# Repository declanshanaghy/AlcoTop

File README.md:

= AUTHOR::
Declan Shanaghy <declan@shanaghy.com>

= DESCRIPTION:
AlcoTop is the XMas drinking cap everyone should have.
With an alcohol sensor and lots of LED's you will know when
you haven't had enough to drink and your way home will be lit before you.

= REQUIREMENTS:
Arduino IDE for loading software onto the chip.
Eagle CAD 6.0+ for reading circuit schematic

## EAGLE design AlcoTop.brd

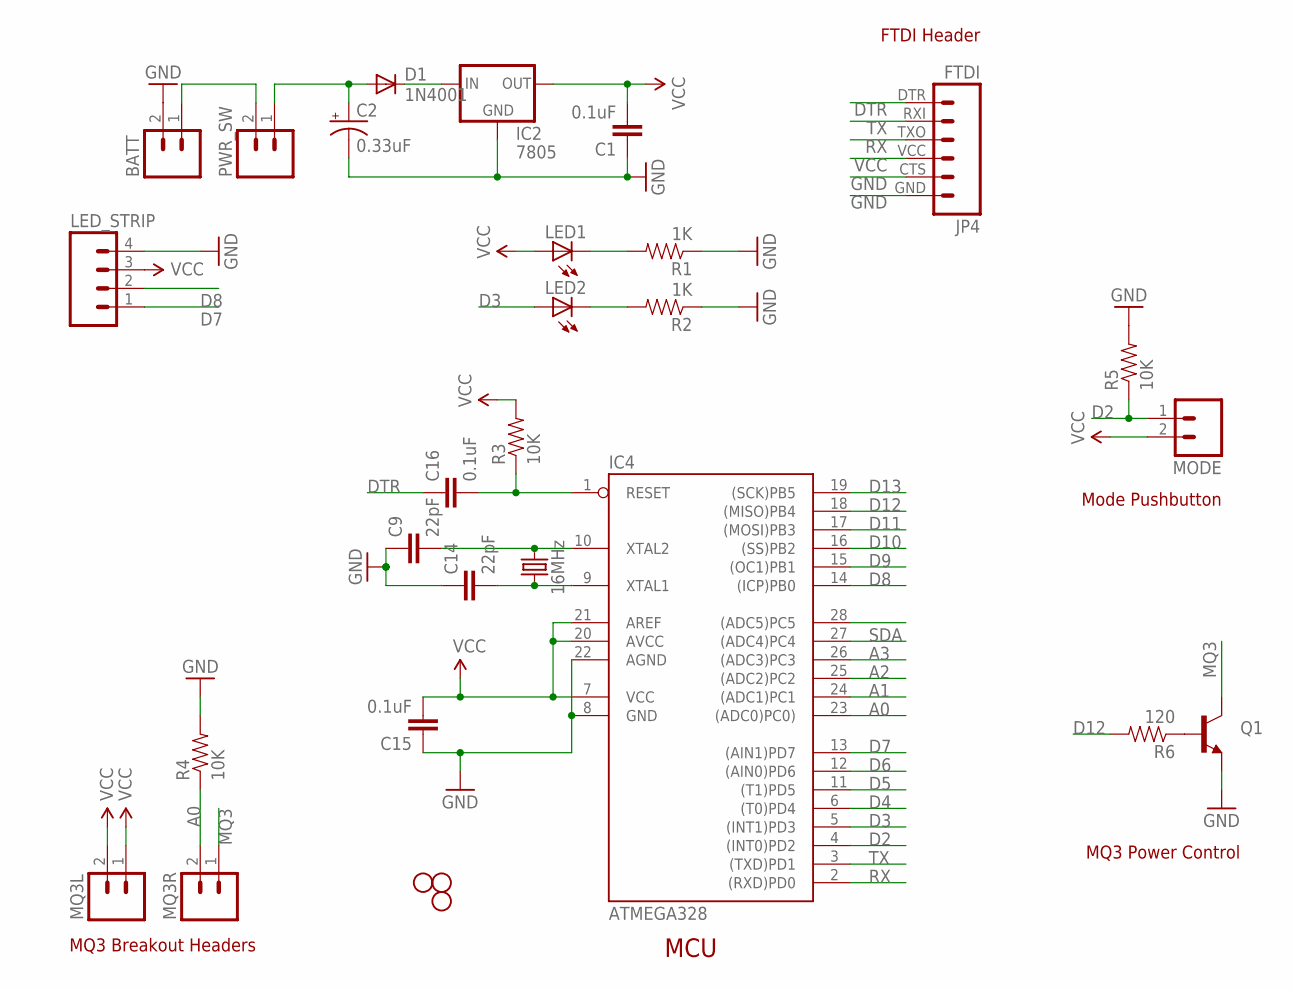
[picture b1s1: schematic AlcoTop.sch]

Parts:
BATT: M02LOCK_LONGPADS; 1X02_LOCK_LONGPADS
C1, C15, C16: 0.1uF; CAP-PTH-SMALL2
C2: 0.33uF; CPOL-RADIAL-10UF-25V
C9, C14: 22pF; CAP-PTH-SMALL2
D1: 1N4001; DIODE-1N4001
IC2: 7805; TO220-IGO
IC4: ATMEGA328; DIL28-3
JP1, JP2, JP6: STAND-OFF#2; STAND-OFF-#2
JP4: FTDI; FTDI_BASIC
LED1, LED2: LED5MM
LED_STRIP: M04LOCK_LONGPADS; 1X04_LOCK_LONGPADS
MODE: M02LOCK_LONGPADS; 1X02_LOCK_LONGPADS
MQ3L, MQ3R: M02LOCK_LONGPADS; 1X02_LOCK_LONGPADS
PWR_SW: M02LOCK_LONGPADS; 1X02_LOCK_LONGPADS
Q1: TRANSISTOR_NPNTO-92-AMMO; TO-92-AMMO
R1, R2: 1K; AXIAL-0.3
R3, R4, R5: 10K; AXIAL-0.3
R6: 120; AXIAL-0.3
Y1: 16MHz; HC49US

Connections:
A0: IC4.23 ((ADC0)PC0)), MQ3R.2, R4.P$1 (1)
A1: IC4.24 ((ADC1)PC1)
A2: IC4.25 ((ADC2)PC2)
A3: IC4.26 ((ADC3)PC3)
D2: IC4.4 ((INT0)PD2), MODE.1, R5.P$1 (1)
D3: IC4.5 ((INT1)PD3), LED2.A
D4: IC4.6 ((T0)PD4)
D5: IC4.11 ((T1)PD5)
D6: IC4.12 ((AIN0)PD6)
D7: IC4.13 ((AIN1)PD7), LED_STRIP.1
D8: IC4.14 ((ICP)PB0), LED_STRIP.2
D9: IC4.15 ((OC1)PB1)
D10: IC4.16 ((SS)PB2)
D11: IC4.17 ((MOSI)PB3)
D12: IC4.18 ((MISO)PB4), R6.P$2 (2)
D13: IC4.19 ((SCK)PB5)
DTR: C16.1, JP4.DTR (1)
GND: BATT.2, C1.1, C2.2 (-), C9.1, C14.1, C15.1, IC2.GND, IC4.8 (GND), IC4.22 (AGND), JP4.CTS (5), JP4.GND (6), LED_STRIP.4, Q1.1 (E), R1.P$1 (1), R2.P$1 (1), R4.P$2 (2), R5.P$2 (2)
MQ3: MQ3R.1, Q1.3 (C)
unnamed: LED1.K (C), R1.P$2 (2)
unnamed: BATT.1, PWR_SW.2
unnamed: C2.1 (+), D1.A, PWR_SW.1
unnamed: LED2.K (C), R2.P$2 (2)
unnamed: D1.C, IC2.IN
unnamed: Q1.2 (B), R6.P$1 (1)
RST: C16.2, IC4.1 (RESET), R3.P$1 (1)
RX: IC4.2 ((RXD)PD0), JP4.TXO (3)
SDA: IC4.27 ((ADC4)PC4)
TX: IC4.3 ((TXD)PD1), JP4.RXI (2)
VCC: C1.2, C15.2, IC2.OUT, IC4.7 (VCC), IC4.20 (AVCC), IC4.21 (AREF), JP4.VCC (4), LED1.A, LED_STRIP.3, MODE.2, MQ3L.1, MQ3L.2, R3.P$2 (2)
XTAL1: C14.2, IC4.9 (XTAL1), Y1.1
XTAL2: C9.2, IC4.10 (XTAL2), Y1.2

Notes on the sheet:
MCU
FTDI Header
Mode Pushbutton
MQ3 Power Control
MQ3 Breakout Headers

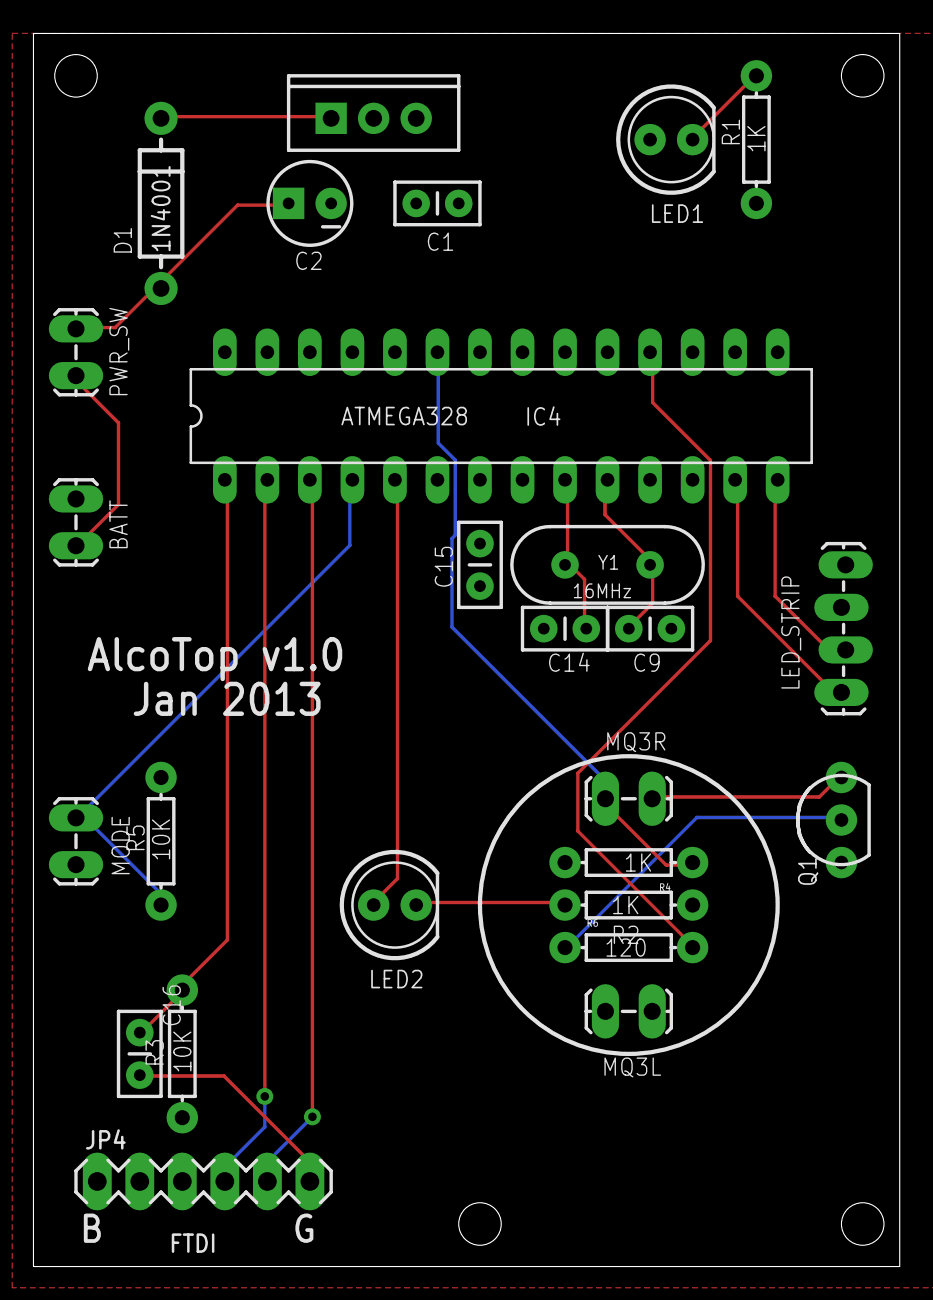
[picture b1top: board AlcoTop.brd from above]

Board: 2 copper layers, 51.7 x 73.7 mm, 30 parts (0 on the bottom side), 21 nets.

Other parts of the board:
JP3: STAND-OFF#2; STAND-OFF-#2

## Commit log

2012-12-04 Initial implementation
2012-12-05 Added transistor switch for MQ3 and pushbutton to change mode. 100mA operating current. YAY
2012-12-07 Switch mode with a single button press. Modes are: random, alco, rainbow, alco, rainbow cycle, alco
2012-12-12 Added funnel and alco read mode on every second click
2012-12-13 Add ability to read the button while taking alcohol readings
2012-12-13 Got rid of all compiler warnings
2012-12-13 Fixed bug which prevented subsequent readings after changing beyond mode 2
2012-12-14 Added mouthpiece funnel. Fixed weirdness in alco sensor readings. Liquid insulator on the 2222PNP was causing it
2013-02-05 Updated board
2013-02-18 Reduced MQ3 voltage divider resistor to 1K
2013-02-18 Bumped version to 1.1
2013-02-18 Tweaked thresholds for 1K resistor

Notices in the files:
parts and their libraries:
SparkFun-DiscreteSemi: Licensing: CC v3.0 Share-Alike You are welcome to use this library for commercial purposes.
